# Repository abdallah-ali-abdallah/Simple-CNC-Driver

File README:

Simple Dual CNC driver (or 4 DC motors) useing 2 L293 chip

This driver can be used to control 2 Bipolar stepper motors (4 wires motor) or it can be used to control 4 DC motors

Included example cods to run the motors (written in both ANSI-C"ATmeal Studio" and Arduino)

All the files (schematics, PCB) designed by EagleCAD 7.3

Licence: Creative common CC-SA-NC

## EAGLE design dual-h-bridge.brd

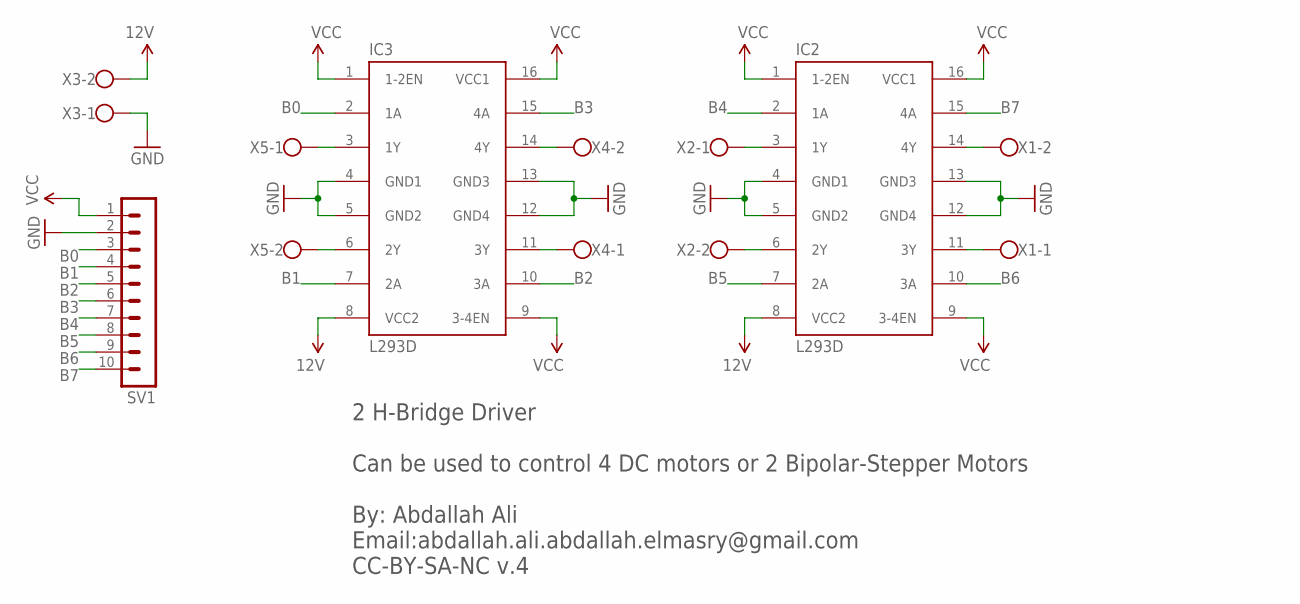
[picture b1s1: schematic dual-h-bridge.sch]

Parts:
IC2, IC3: L293D; DIL16
SV1: MA10-1
X1, X2, X3, X4, X5: W237-102

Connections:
12V: IC2.8 (VCC2), IC3.8 (VCC2), X3.2
B0: IC3.2 (1A), SV1.3
B1: IC3.7 (2A), SV1.4
B2: IC3.10 (3A), SV1.5
B3: IC3.15 (4A), SV1.6
B4: IC2.2 (1A), SV1.7
B5: IC2.7 (2A), SV1.8
B6: IC2.10 (3A), SV1.9
B7: IC2.15 (4A), SV1.10
GND: IC2.4 (GND1), IC2.5 (GND2), IC2.12 (GND4), IC2.13 (GND3), IC3.4 (GND1), IC3.5 (GND2), IC3.12 (GND4), IC3.13 (GND3), SV1.2, X3.1
unnamed: IC3.3 (1Y), X5.1
unnamed: IC2.3 (1Y), X2.1
unnamed: IC2.6 (2Y), X2.2
unnamed: IC2.11 (3Y), X1.1
unnamed: IC2.14 (4Y), X1.2
unnamed: IC3.6 (2Y), X5.2
unnamed: IC3.11 (3Y), X4.1
unnamed: IC3.14 (4Y), X4.2
VCC: IC2.1 (1-2EN), IC2.9 (3-4EN), IC2.16 (VCC1), IC3.1 (1-2EN), IC3.9 (3-4EN), IC3.16 (VCC1), SV1.1

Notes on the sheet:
2 H-Bridge Driver Can be used to control 4 DC motors or 2 Bipolar-Stepper Motors By: Abdallah Ali Email:abdallah.ali.abdallah.elmasry@gmail.com CC-BY-SA-NC v.4

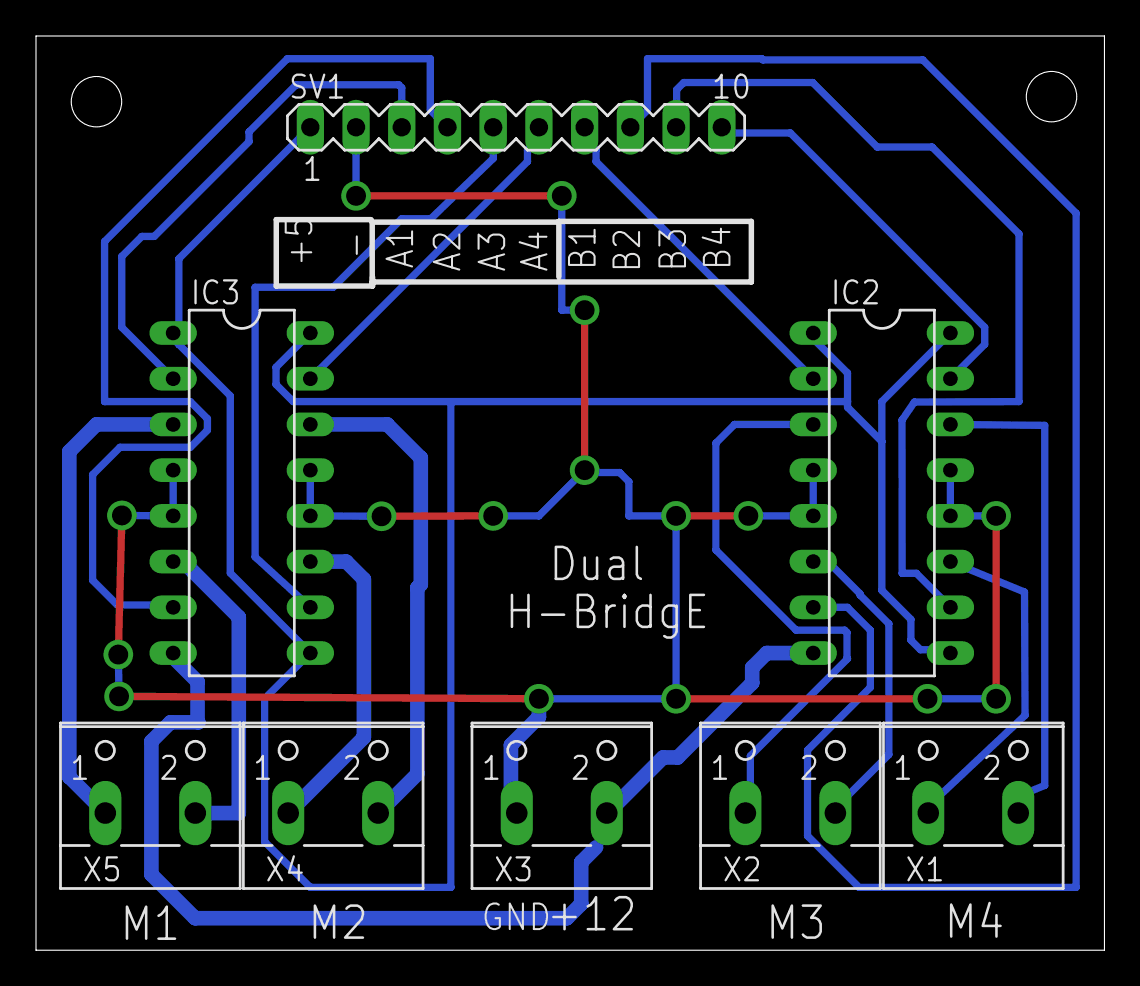
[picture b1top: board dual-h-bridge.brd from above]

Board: 2 copper layers, 59.4 x 50.8 mm, 8 parts (0 on the bottom side), 19 nets.

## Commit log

2015-06-13 Schematic File - EagleCAD 7.3
2015-06-13 PCB file - EagleCAD 7.3
2015-06-13 Bottom layer - printable file using toner tansfer methode
2015-06-13 Schematics in PNG formate
2015-06-13 Top layer
2015-06-13 Mirrored Top Layer
2015-06-13 Example code to run the CNC with variable speed
2015-06-13 README
2015-06-13 top view
2015-06-13 Arduino Example Code

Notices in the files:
parts and their libraries:
SparkFun-Aesthetics: Licensing: Creative Commons ShareAlike 4.0 International - https://creativecommons.org/licenses/by-sa/4.0
